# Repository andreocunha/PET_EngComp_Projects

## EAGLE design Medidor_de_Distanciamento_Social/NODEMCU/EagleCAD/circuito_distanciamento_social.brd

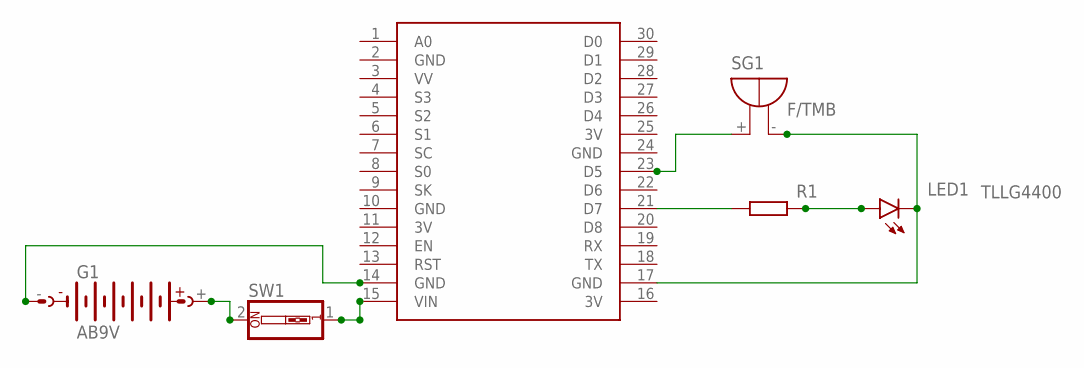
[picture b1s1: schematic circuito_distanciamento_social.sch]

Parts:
G1: AB9V
LED1: TLLG4400; LED3MM
R1: R-EU_0207/10; 0207/10
SG1: F/TMB
SW1: SW_DIP-1; EDG-01
U$1: NODEMCU

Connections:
3V: U$1.11 (3V), U$1.16 (3V), U$1.25 (3V)
GND: U$1.2 (GND), U$1.10 (GND), U$1.24 (GND)
unnamed: R1.1, U$1.21 (D7)
unnamed: LED1.K (C), SG1.-, U$1.17 (GND)
unnamed: SG1.+, U$1.23 (D5)
unnamed: LED1.A, R1.2
unnamed: G1.+, SW1.2
unnamed: G1.-, U$1.14 (GND)
unnamed: SW1.1, U$1.15 (VIN)

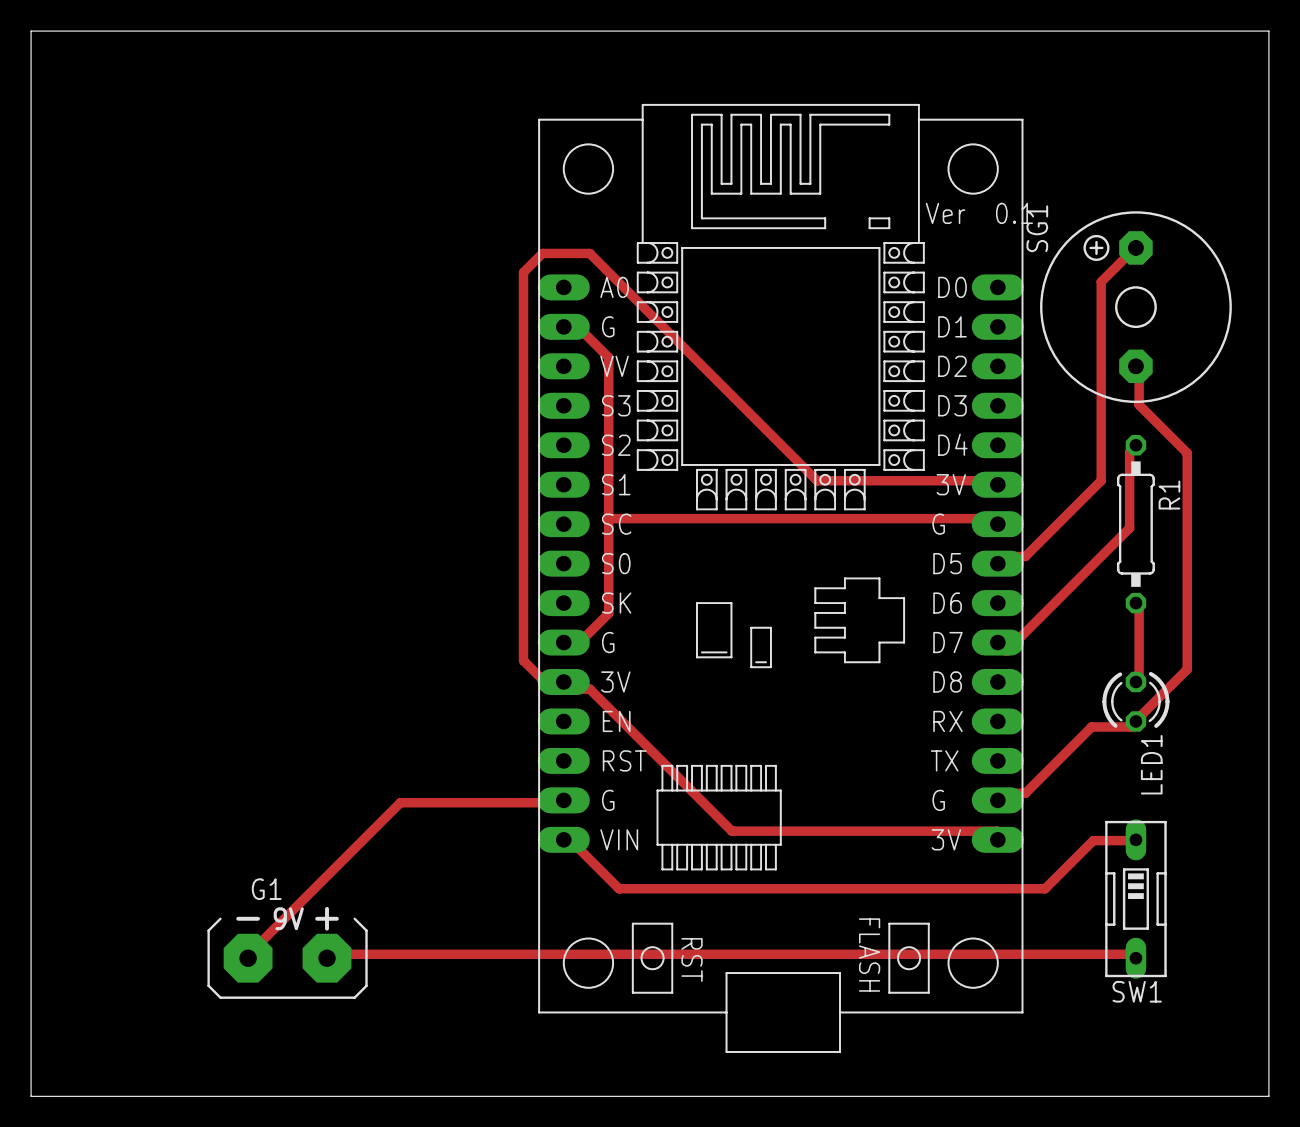
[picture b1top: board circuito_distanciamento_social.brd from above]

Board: 2 copper layers, 79.7 x 68.6 mm, 6 parts (0 on the bottom side), 9 nets.

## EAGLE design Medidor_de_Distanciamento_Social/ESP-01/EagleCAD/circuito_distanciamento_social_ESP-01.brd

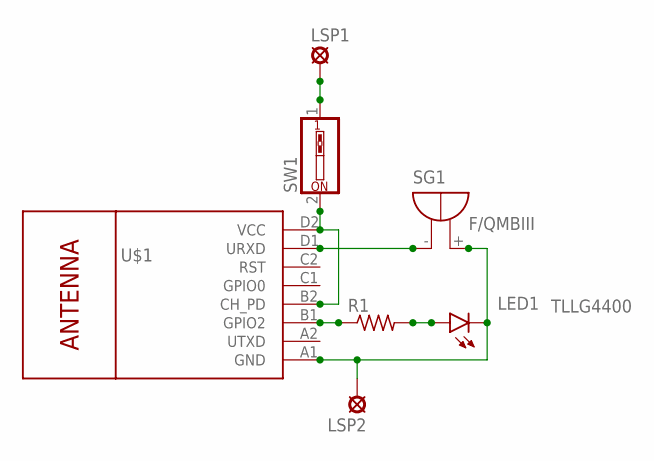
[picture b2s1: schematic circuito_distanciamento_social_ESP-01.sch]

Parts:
LED1: TLLG4400; LED3MM
LSP1, LSP2: LSP13
R1: R-US_0204/7; 0204/7
SG1: F/QMBIII
SW1: SW_DIP-1; EDG-01
U$1: WIRELESS-WIFI-ESP-01

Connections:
unnamed: SW1.2, U$1.B2 (CH_PD), U$1.D2 (VCC)
unnamed: R1.1, U$1.B1 (GPIO2)
unnamed: LED1.A, R1.2
unnamed: SG1.- (+), U$1.D1 (URXD)
unnamed: LSP1.MP, SW1.1
unnamed: LED1.K (C), LSP2.MP, SG1.+ (-), U$1.A1 (GND)

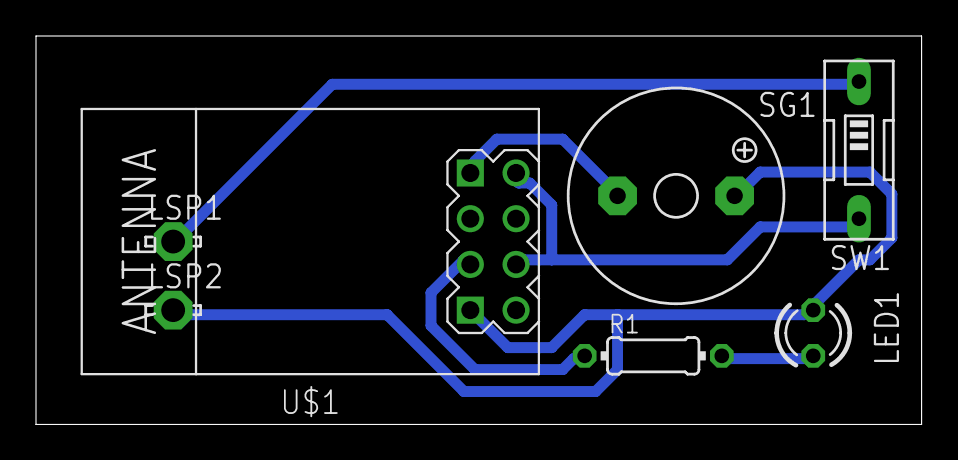
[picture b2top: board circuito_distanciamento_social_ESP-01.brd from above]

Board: 2 copper layers, 49.2 x 21.6 mm, 7 parts (0 on the bottom side), 6 nets.

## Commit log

2020-05-30 Medidor de Distanciamento Social
    Circuito criado para manter a segurança entre as pessoas durante o período de pandemia do COVID-19
2020-05-30 Tranca Biométrica com RFID
2020-05-30 Versão 2.0 da tranca biométrica com RFID
2020-05-30 KiCad - Modelo 3D do Circuito
2020-05-30 Imagem do modelo 3D feito no KiCad
2020-08-02 Aumento na velocidade de detecção
2020-08-06 Definindo canal de leitura e busca
2020-08-07 Comentários no código

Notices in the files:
parts and their libraries:
diy-modules: Released under the Creative Commons Attribution 4.0 International License: http://creativecommons.org/licenses/by/4.0
